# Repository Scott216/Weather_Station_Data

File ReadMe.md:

This project received Davis VantagePro wireless weather station data and sends to to Weather Underground's personal weather station (PWS).
It uses as Moteino (Arduino Uno + radio transceiver), WIZ811MJ Ethernet module and BMP180 pressure sensor <br>
See the [wiki](https://github.com/Scott216/Weather_Station_Data/wiki) for details.

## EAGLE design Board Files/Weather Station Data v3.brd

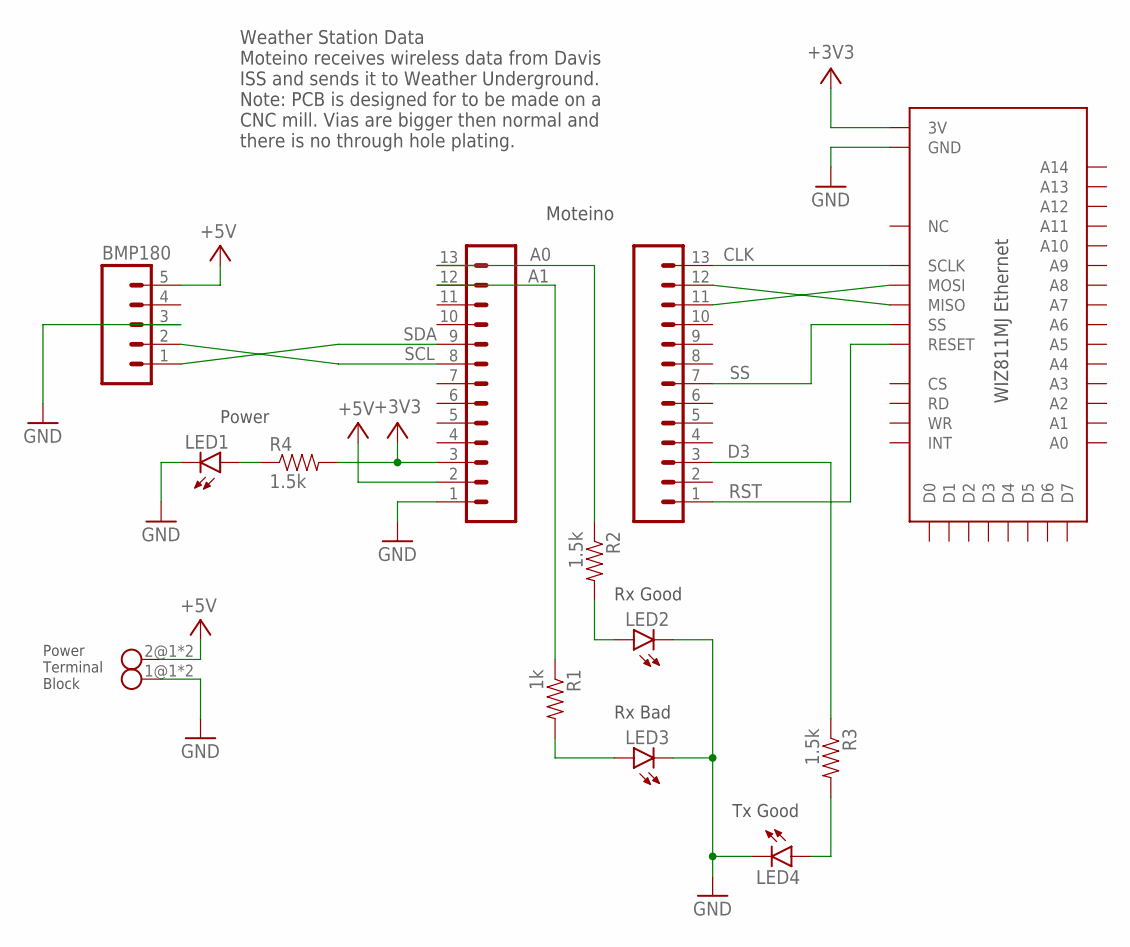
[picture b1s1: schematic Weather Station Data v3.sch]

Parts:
BMP180: M05PTH_LONGPADS; 1X05_LONGPADS
JP1, JP2: M13LONGPADS; 1X13-LONGPADS
LED1, LED2, LED4: 754-1440-1-ND; LED-1206
LED3: 754-1143-1-ND; LED-1206
POWER: SPRING_TB_RT2
R1: 1k; AXIAL-0.3
R2, R3, R4: 1.5k; AXIAL-0.3
U$1: WIZ811MJ

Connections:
+3V3: JP1.3, R4.P$2 (2), U$1.3V@1 (3V), U$1.3V@2 (3V)
+5V: BMP180.5, JP1.2, POWER.2@1, POWER.2@2
A0: JP1.13, R2.P$1 (1)
A1: JP1.12, R1.P$1 (1)
CLK: JP2.13, U$1.SCLK
D3: JP2.3, R3.P$1 (1)
GND: BMP180.3, JP1.1, LED1.C, LED2.C, LED3.C, LED4.C, POWER.1@1, POWER.1@2, U$1.GND@1 (GND), U$1.GND@2 (GND), U$1.GND@3 (GND), U$1.GND@4 (GND), U$1.GND@5 (GND)
MISO: JP2.12, U$1.MISO
MOSI: JP2.11, U$1.MOSI
unnamed: LED1.A, R4.P$1 (1)
unnamed: LED2.A, R2.P$2 (2)
unnamed: LED4.A, R3.P$2 (2)
unnamed: LED3.A, R1.P$2 (2)
RST: JP2.1, U$1.RESET
SCL: BMP180.2, JP1.8
SDA: BMP180.1, JP1.9
SS: JP2.7, U$1.SCS (SS)

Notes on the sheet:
Weather Station Data Moteino receives wireless data from Davis ISS and sends it to Weather Underground. Note: PCB is designed for to be made on a CNC mill. Vias are bigger then normal and there is no through hole plating.
Moteino
Power
Rx Good
Rx Bad
Tx Good
Power Terminal Block

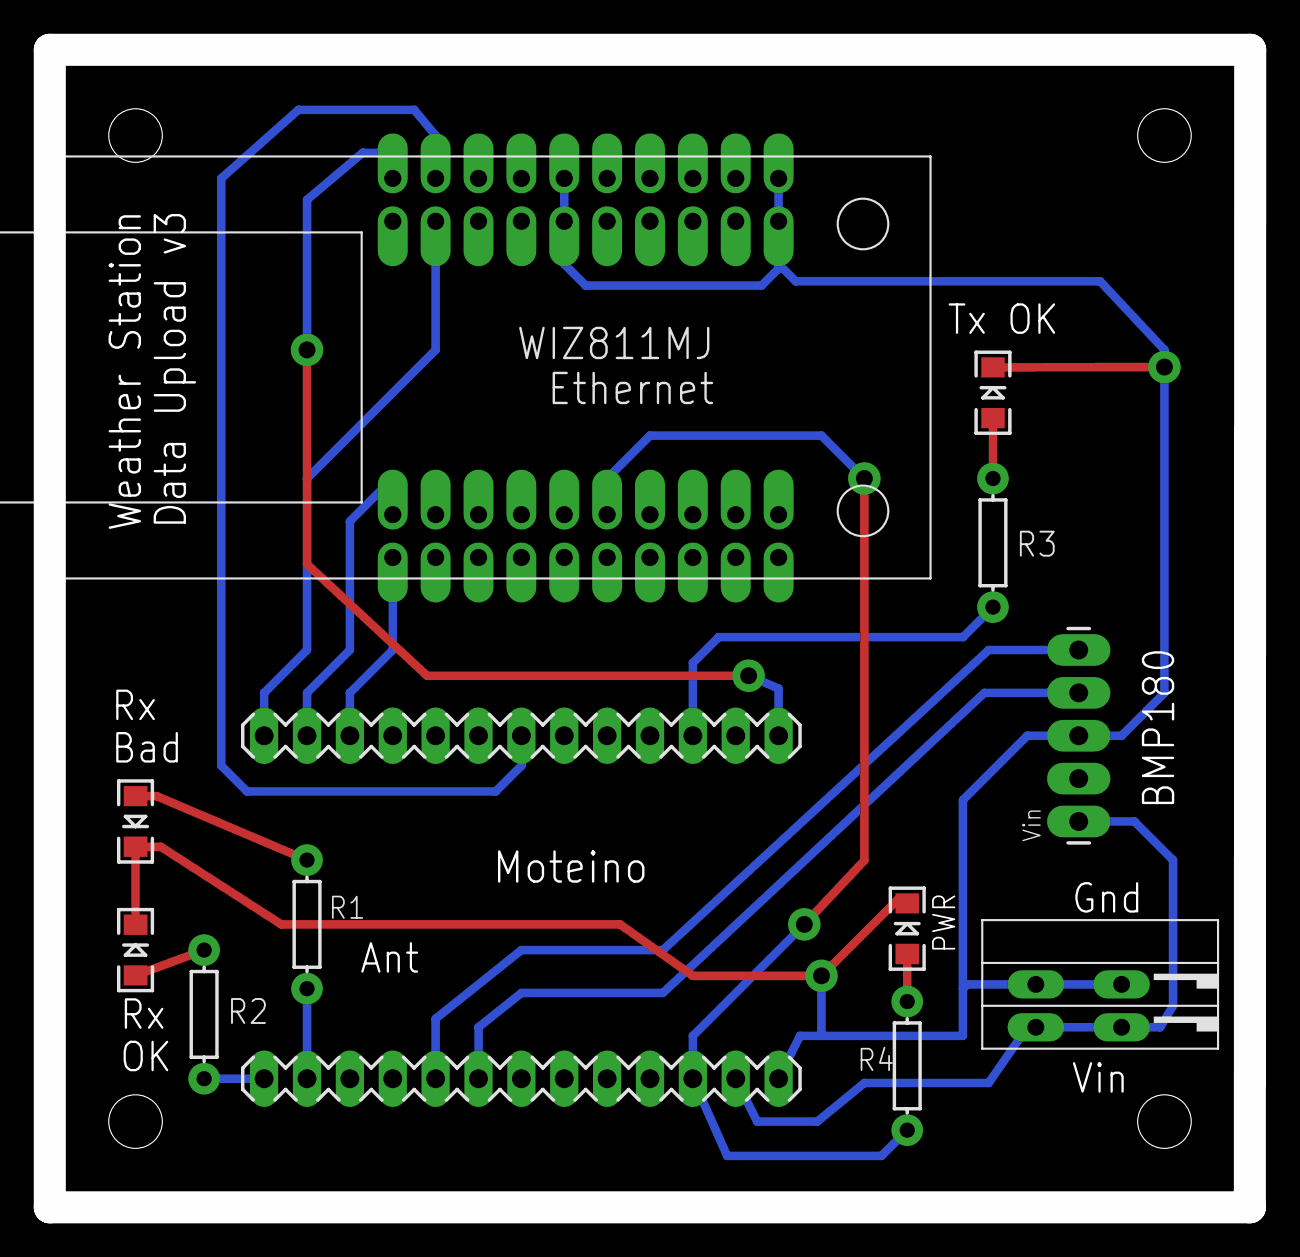
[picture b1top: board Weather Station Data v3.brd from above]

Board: 2 copper layers, 71.1 x 68.6 mm, 13 parts (0 on the bottom side), 17 nets.

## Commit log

2014-07-07 orig file from dekay
2014-07-07 Orig file from delay
2014-07-20 v0.1 - getting VSS data and can upload
    Gets VSS weather station data and can upload to Weather Underground
    test station. Don’t have barometer sensor yet and haven’t tested radio
    with upload yet.
2014-07-20 empty read me
2014-07-20 Modified Ethernet.h library
    This library lets user choose different slave select pin. Normally
    it’s D10.
2014-07-21 Initial Readme file
2014-07-21 added still debugging line
2014-07-23 Interrupts work-around
    Disabled interrupts in w5100.cpp for setSS(), then re-enabled them in
    resetSS()
2014-07-23 V0.11 - working
    Working version. Don’t have pressure sensor hooked up yet
2014-07-24 Pinout
2014-07-24 v0.13 changed rainrate calculation
    changed rain rate to 5 minute tracking, added station ID check
2014-07-29 v15 - moved Tx OK LED to D3, minor edits
2014-07-29 Original Ethernet library files
2014-07-29 Modified Ethernet library files
    Added slave select ability and disabled interrupts
2014-07-29 v0.16 formatting and some cleanup
2014-07-30 Schematic and PCB Files
2014-07-30 Put ethernet files in directory
2014-07-30 Formatting readme
2014-07-30 Moved info to Wiki
2014-07-30 Pics of hardware
2014-08-07 v0.18 - changed rain calc
    Changed hourly rain rate calculation. Was based on 5 minutes of rain,
    now it 15 minutes
2014-08-09 v0.19 fixed barometer calc
    Adjusted barometer for sea level
2014-08-22 v0.20 fixed rain accum bug
    Davis ISS rain counter rolls over at 127, not 255 like I assumed. I
    also changed my station ID to 3
2014-09-14 Added info about library mods
2014-09-14 v24 - new rain rate calc
2014-10-08 v29 changed rain rate calc, getting gusts from ISS
    Using rain rate and gusts from ISS instead of calculating in code
2014-10-08 fixed pinMode bug
    Couldn’t use static IP because of a missing pinMode() for SS pin
2014-10-08 v0.30 - cleanup
    Removed unused code. Various comment and formatting changes
2014-10-17 v0.32 Fixed wind averaging
2014-10-18 Removed an old comment
2014-10-26 Fixed wind direction bug
2014-12-23 v0.37 - See change log
    Adjusted rain rate formula, enabled pull-ups in SS pins, reboot
    counter, Heartbeat LED
2014-12-24 v0.38 Redid print debug, read daily rain from WU
    Made reboot counter in EEPROM an integer instead of a byte. Redid
    output for PRINT_DEBUG. Made it a tab delimited table.
    On startup get get daily rain accumulation from Weather Underground
2015-01-04 v0.39 minor tweaks
    Added 2 second delay after Udp.begin to see if it helped reduce serial
    monitor jibberish - didn’t help
2015-01-20 v0.43 - added WDT
    See change log v0.40 to v0.43
2015-01-30 Initial Commit
    These are DeKay’s RFM69 library files from early 2014
2015-01-30 v0.44 - packet interval change
    Changed packet interval from 2555 to formula. Change millis() to
    micros()/1000 because micros is more accurate
2015-01-30 Results of testing different packet intervals
    Increased interval for 1mS and every 10 minutes, then counted number of
    good packets received over the 10 minutes. Sketch ran for a couple
    days.
2015-01-30 Added MoteinoMega compatibility and some SPI changes
    Made changes so library would work with MoteinoMega
    - Added statement to insure slave select pin would be high
    - Slowed down SPI speed
    - Moved SPI.setDataMode(), SPI.setBitOrder(), SPI.setClockDivider from
    initialize() to interruptHandler()
    These changes reflect some of the changes in the LowPowerLabs RFM69
2015-01-30 Renamed readme.md to Readme_Dekay.txt
2015-03-23 v0.46 - added ifdef for MoteinoMega
2015-06-21 v0.47 - delay in reboot
    Needed delay in reboot so serial monitor could display message before
    Arduino rebooted.
2015-07-10 v0.49 Lots of NTP time server changed
2015-07-10 New sketch to test radio only
2015-07-10 Output showing CRC errors
2015-09-02 v0.51 new Dekay RFM69 library
2017-12-21 Testing Ethernet library mods
2017-12-21 Initial commit for WDT
    Code to use ATTiny as a watchdog timer. Haven’t tested it yet
2017-12-21 Initial Commit - testing Ethernet
2017-12-21 Debugging scripts
2017-12-21 Xcode stuff
2017-12-21 Initial commit to test which moteino board is being used.
    Can detect if it’s a MoteinoMega with __AVR_ATmega1284__
2017-12-21 v0.55 - fixed NTP problem and WU GET request format
    Changed NTP so it used a URL instead of IP addresses.
    March 2017 Weather Underground switched AWS and the get request format
    had to be updated.
2017-12-22 v0.57 - got working again
    Changed NTP from IP to a url. Fixed updated GET request format -
    changed when Weather Underground moved to AWS servers.
2017-12-23 v0.58 - more tries for NTP time and getting daily rain on startup
2017-12-23 Initial commit
    Schematic for MoteinoMega
2018-01-11 v0.61
2018-11-10 v0.63 WDT Testing

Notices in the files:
parts and their libraries:
SparkFun-Connectors: Licensing: Creative Commons ShareAlike 4.0 International - https://creativecommons.org/licenses/by-sa/4.0
